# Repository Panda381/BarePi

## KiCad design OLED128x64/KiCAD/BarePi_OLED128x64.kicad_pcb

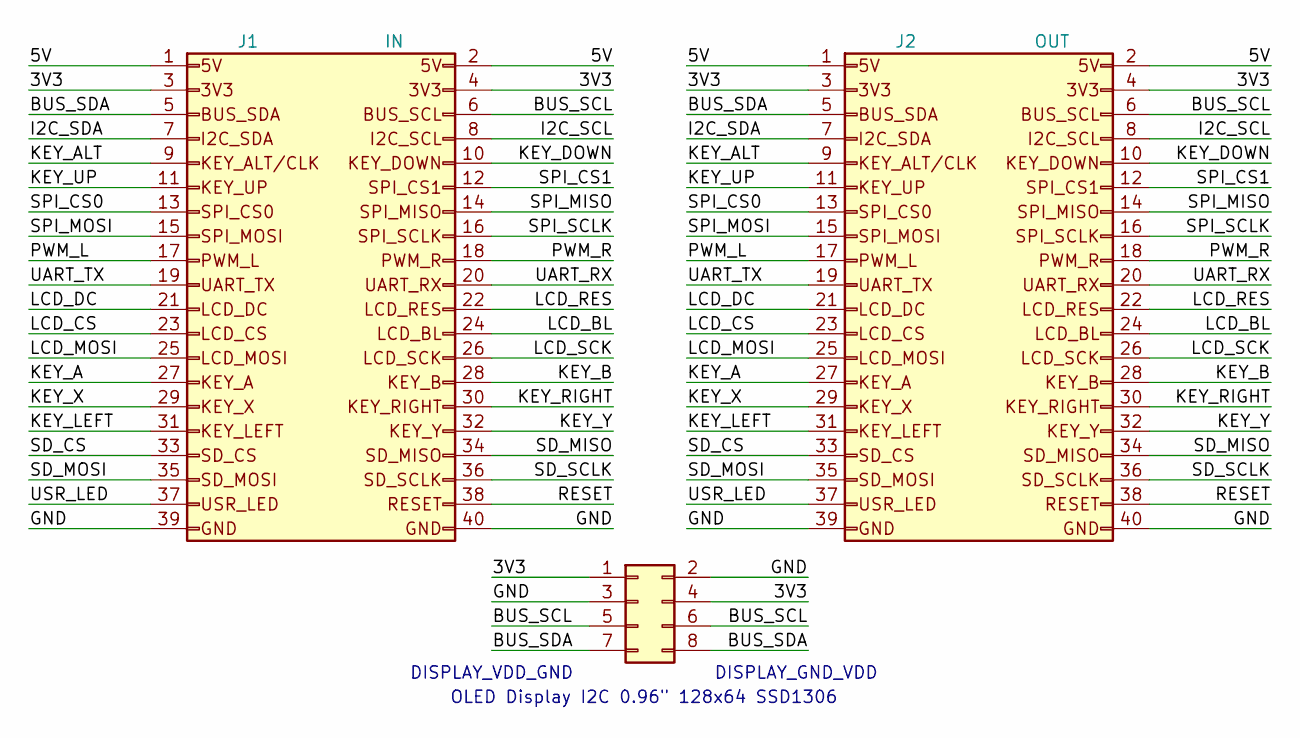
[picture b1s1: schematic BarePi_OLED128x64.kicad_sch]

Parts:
J1: IN; Raspberry_IN_PinHeader_2x20_P2.54mm_Horizontal
J2: OUT; Raspberry_OUT_PinSocket_2x20_P2.54mm_Horizontal
J3: DISPLAY; Raspberry_PinSocket_2x04_P2.54mm_Vertical

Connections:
/3V3: J1.3, J1.4, J2.3, J2.4, J3.1, J3.4
/5V: J1.1, J1.2, J2.1, J2.2
/BUS_SCL: J1.6, J2.6, J3.5, J3.6
/BUS_SDA: J1.5, J2.5, J3.7, J3.8
/GND: J1.39, J1.40, J2.39, J2.40, J3.2, J3.3
/I2C_SCL: J1.8, J2.8
/I2C_SDA: J1.7, J2.7
/KEY_A: J1.27, J2.27
/KEY_ALT: J1.9, J2.9
/KEY_B: J1.28, J2.28
/KEY_DOWN: J1.10, J2.10
/KEY_LEFT: J1.31, J2.31
/KEY_RIGHT: J1.30, J2.30
/KEY_UP: J1.11, J2.11
/KEY_X: J1.29, J2.29
/KEY_Y: J1.32, J2.32
/LCD_BL: J1.24, J2.24
/LCD_CS: J1.23, J2.23
/LCD_DC: J1.21, J2.21
/LCD_MOSI: J1.25, J2.25
/LCD_RES: J1.22, J2.22
/LCD_SCK: J1.26, J2.26
/PWM_L: J1.17, J2.17
/PWM_R: J1.18, J2.18
/RESET: J1.38, J2.38
/SD_CS: J1.33, J2.33
/SD_MISO: J1.34, J2.34
/SD_MOSI: J1.35, J2.35
/SD_SCLK: J1.36, J2.36
/SPI_CS0: J1.13, J2.13
/SPI_CS1: J1.12, J2.12
/SPI_MISO: J1.14, J2.14
/SPI_MOSI: J1.15, J2.15
/SPI_SCLK: J1.16, J2.16
/UART_RX: J1.20, J2.20
/UART_TX: J1.19, J2.19
/USR_LED: J1.37, J2.37

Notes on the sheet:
OLED Display I2C 0.96{dblquote} 128x64 SSD1306
DISPLAY_VDD_GND
DISPLAY_GND_VDD

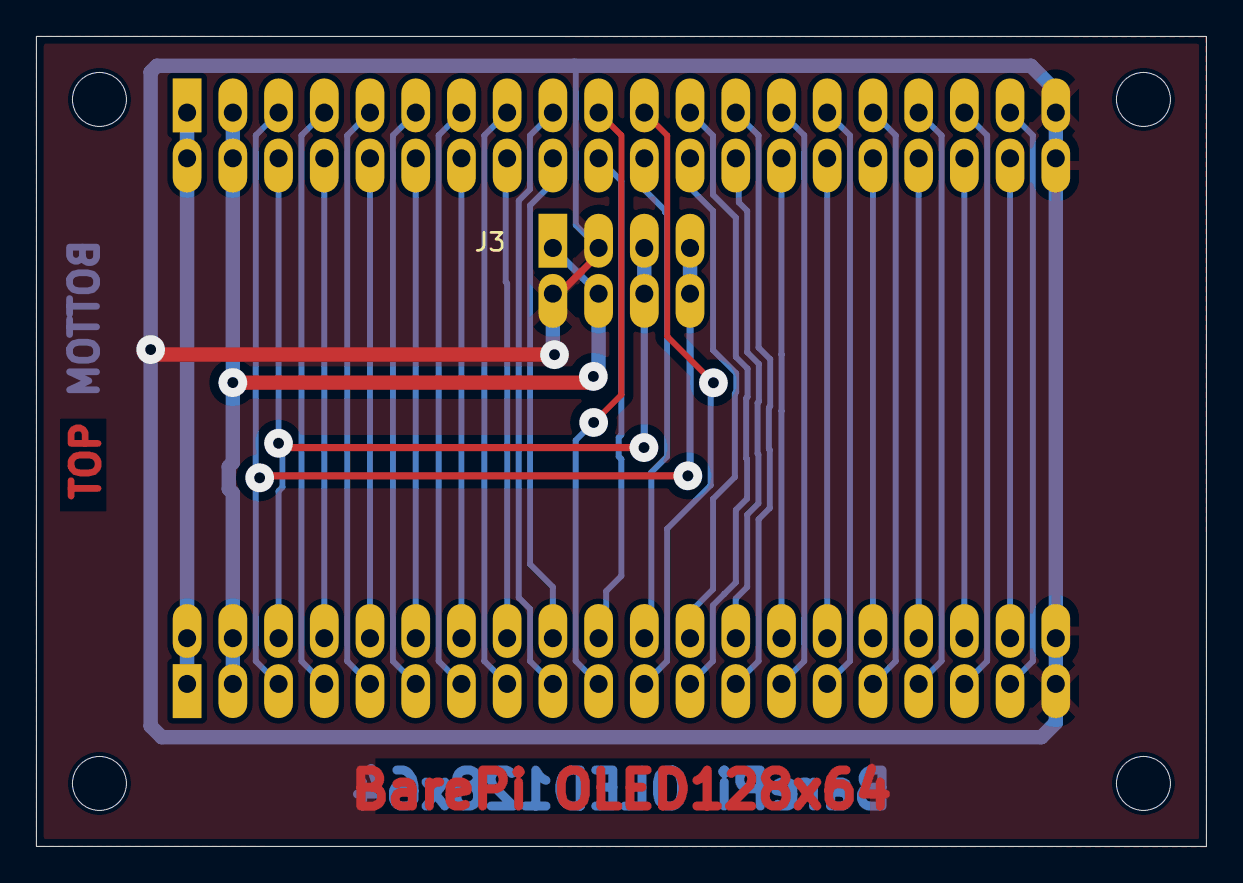
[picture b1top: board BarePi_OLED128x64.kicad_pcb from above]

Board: 2 copper layers, 65.0 x 45.0 mm, 3 parts (0 on the bottom side), 37 nets.

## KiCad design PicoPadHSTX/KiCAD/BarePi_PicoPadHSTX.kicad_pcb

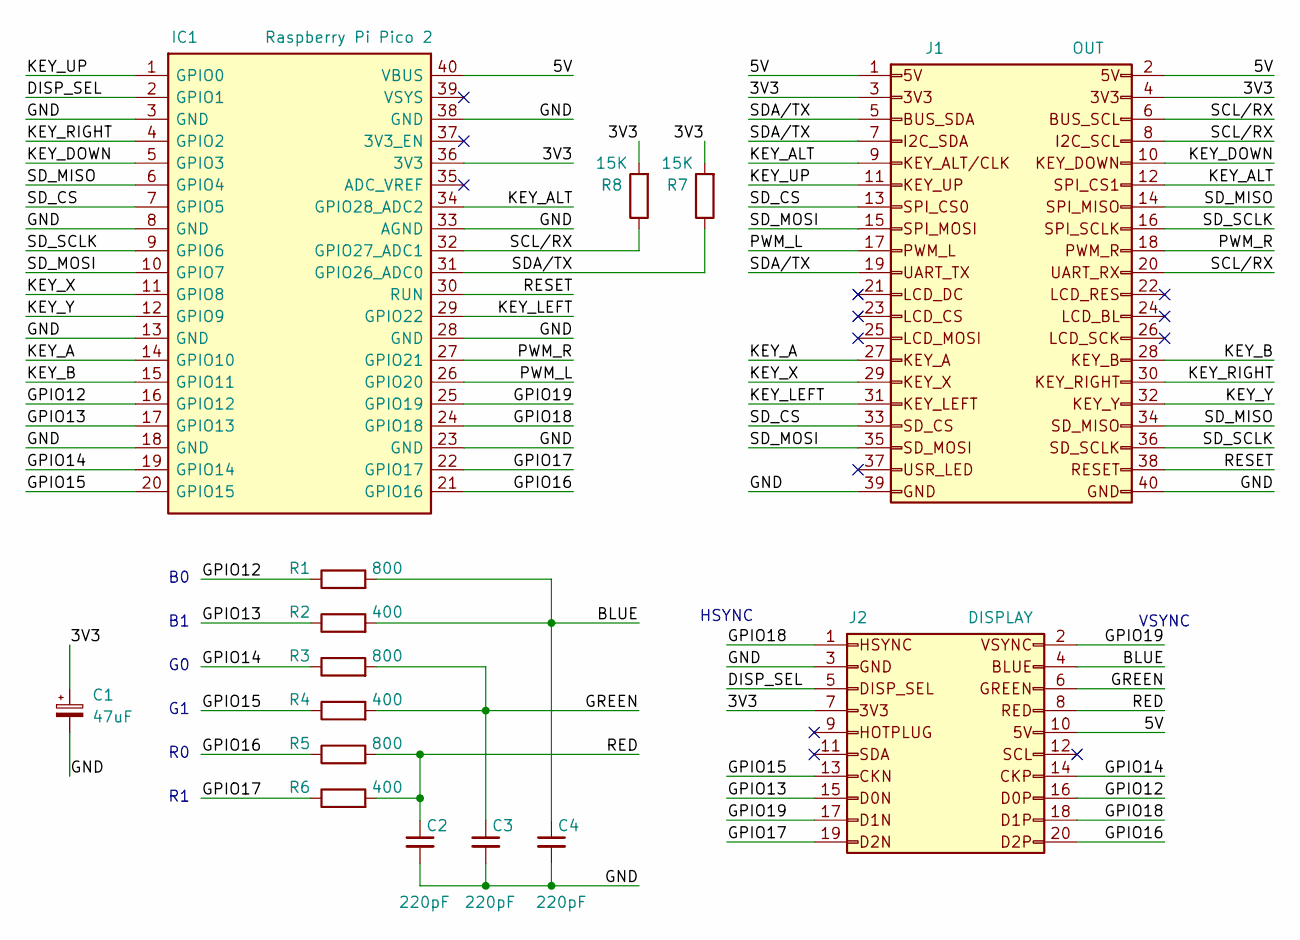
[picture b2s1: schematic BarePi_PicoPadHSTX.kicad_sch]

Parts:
C1: 47uF; CP_EIA-3216-18_Kemet-A_HandSolder
C2, C3, C4: 220pF; C_1206_3216Metric_Pad1.33x1.80mm_HandSolder
IC1: Raspberry Pi Pico 2; Raspberry_Pi_Pico_Common_Unspecified
J1: OUT; Raspberry_OUT_PinSocket_2x20_P2.54mm_Horizontal
J2: DISPLAY; Raspberry_OUT_PinSocket_2x10_P2.54mm_Horizontal
R1, R3, R5: 800; R_0805_2012Metric_Pad1.20x1.40mm_HandSolder
R2, R4, R6: 400; R_0805_2012Metric_Pad1.20x1.40mm_HandSolder
R7, R8: 15K; R_1206_3216Metric_Pad1.30x1.75mm_HandSolder

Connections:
/3V3: C1.1, IC1.36 (3V3), J1.3, J1.4, J2.7, R7.2, R8.2
/5V: IC1.40 (VBUS), J1.1, J1.2, J2.10
/BLUE: C4.1, J2.4, R1.2, R2.2
/DISP_SEL: IC1.2 (GPIO1), J2.5
/GND: C1.2, C2.2, C3.2, C4.2, IC1.3 (GND), IC1.8 (GND), IC1.13 (GND), IC1.18 (GND), IC1.23 (GND), IC1.28 (GND), IC1.33 (AGND), IC1.38 (GND), J1.39, J1.40, J2.3
/GPIO12: IC1.16 (GPIO12), J2.16, R1.1
/GPIO13: IC1.17 (GPIO13), J2.15, R2.1
/GPIO14: IC1.19 (GPIO14), J2.14, R3.1
/GPIO15: IC1.20 (GPIO15), J2.13, R4.1
/GPIO16: IC1.21 (GPIO16), J2.20, R5.1
/GPIO17: IC1.22 (GPIO17), J2.19, R6.1
/GPIO18: IC1.24 (GPIO18), J2.1, J2.18
/GPIO19: IC1.25 (GPIO19), J2.2, J2.17
/GREEN: C3.1, J2.6, R3.2, R4.2
/KEY_A: IC1.14 (GPIO10), J1.27
/KEY_ALT: IC1.34 (GPIO28_ADC2), J1.9, J1.12
/KEY_B: IC1.15 (GPIO11), J1.28
/KEY_DOWN: IC1.5 (GPIO3), J1.10
/KEY_LEFT: IC1.29 (GPIO22), J1.31
/KEY_RIGHT: IC1.4 (GPIO2), J1.30
/KEY_UP: IC1.1 (GPIO0), J1.11
/KEY_X: IC1.11 (GPIO8), J1.29
/KEY_Y: IC1.12 (GPIO9), J1.32
/PWM_L: IC1.26 (GPIO20), J1.17
/PWM_R: IC1.27 (GPIO21), J1.18
/RED: C2.1, J2.8, R5.2, R6.2
/RESET: IC1.30 (RUN), J1.38
/SCL/RX: IC1.32 (GPIO27_ADC1), J1.6, J1.8, J1.20, R8.1
/SDA/TX: IC1.31 (GPIO26_ADC0), J1.5, J1.7, J1.19, R7.1
/SD_CS: IC1.7 (GPIO5), J1.13, J1.33
/SD_MISO: IC1.6 (GPIO4), J1.14, J1.34
/SD_MOSI: IC1.10 (GPIO7), J1.15, J1.35
/SD_SCLK: IC1.9 (GPIO6), J1.16, J1.36

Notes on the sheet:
VSYNC
HSYNC

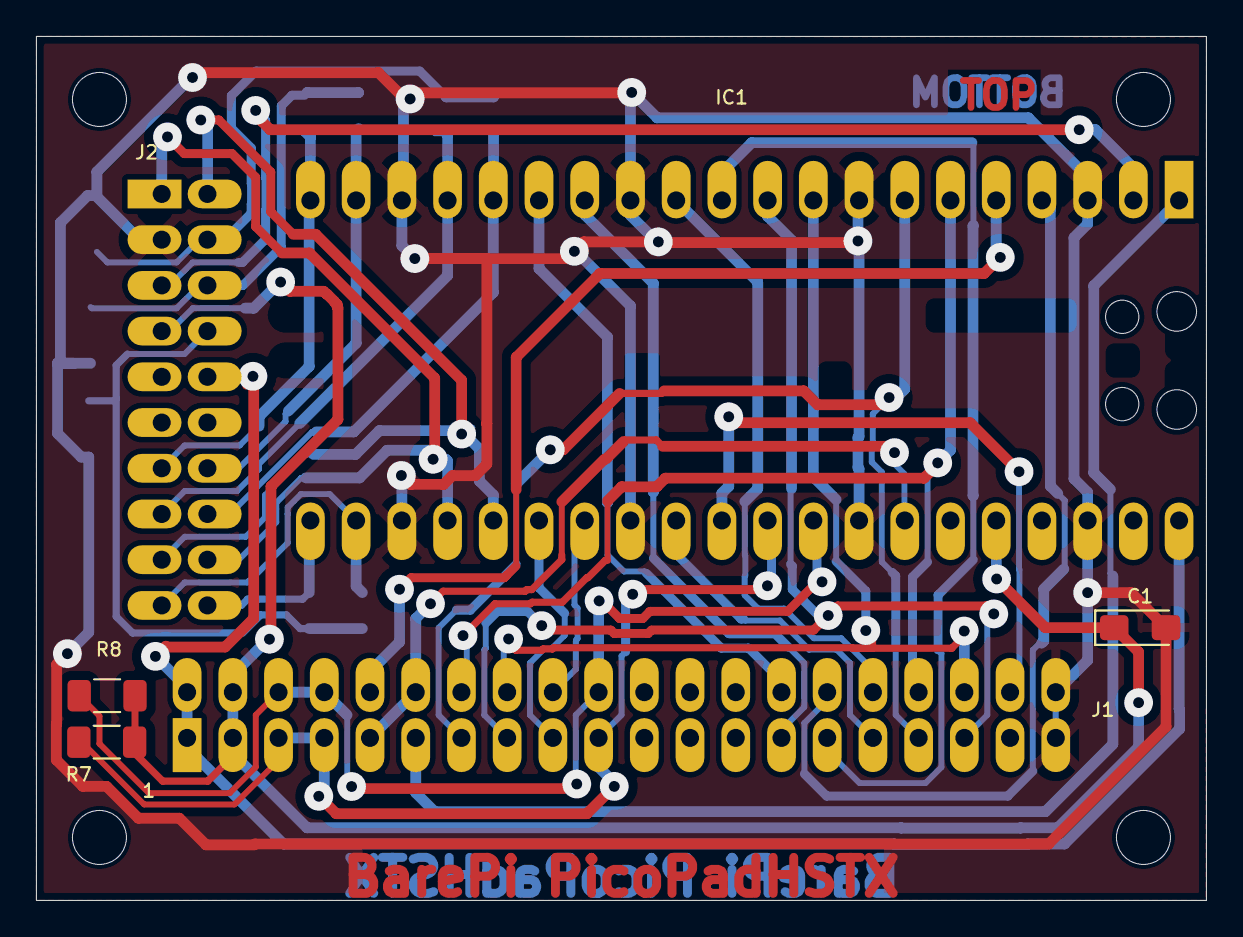
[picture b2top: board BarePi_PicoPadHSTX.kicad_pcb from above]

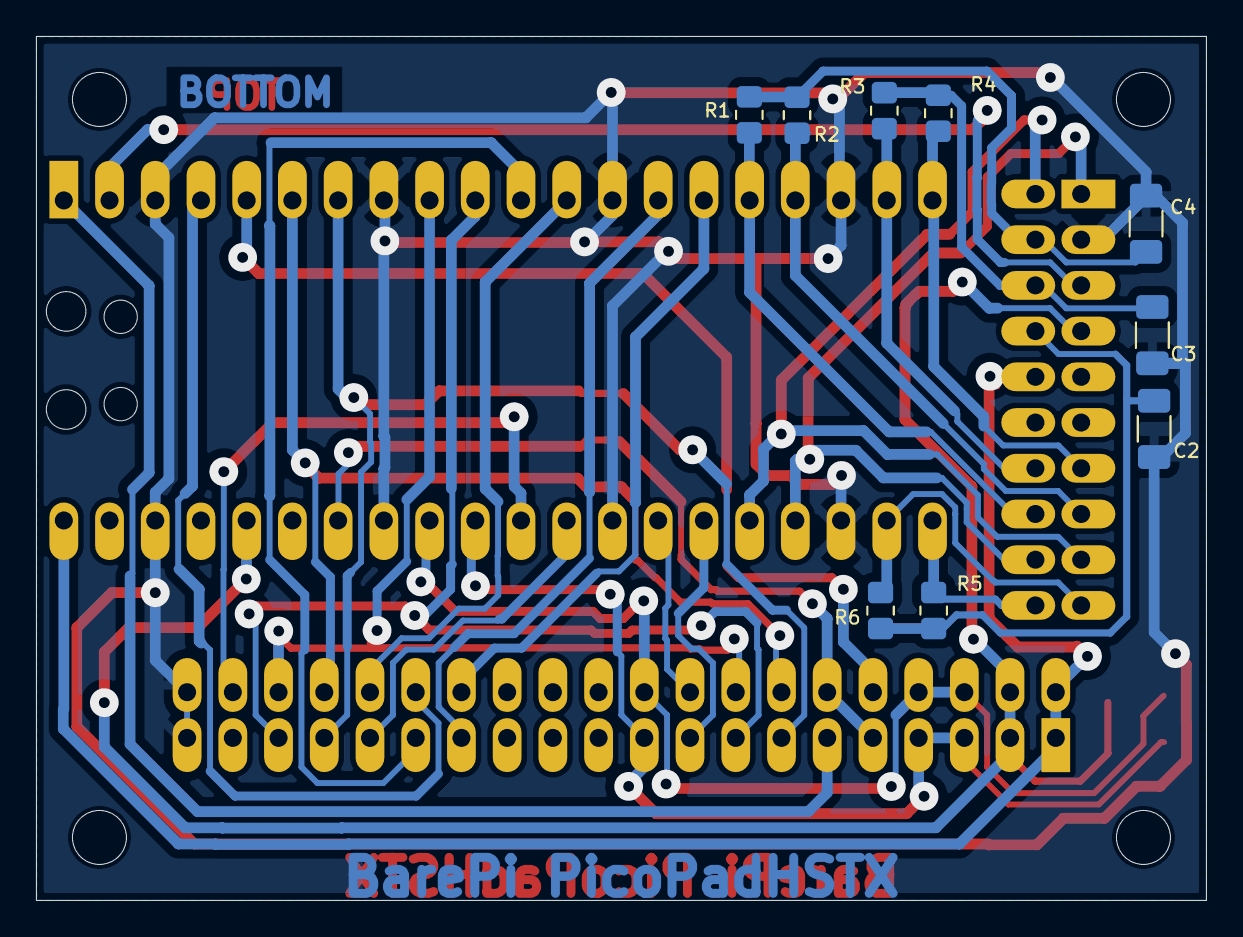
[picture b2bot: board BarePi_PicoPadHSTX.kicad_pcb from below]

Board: 2 copper layers, 65.0 x 48.0 mm, 15 parts (9 on the bottom side), 33 nets.

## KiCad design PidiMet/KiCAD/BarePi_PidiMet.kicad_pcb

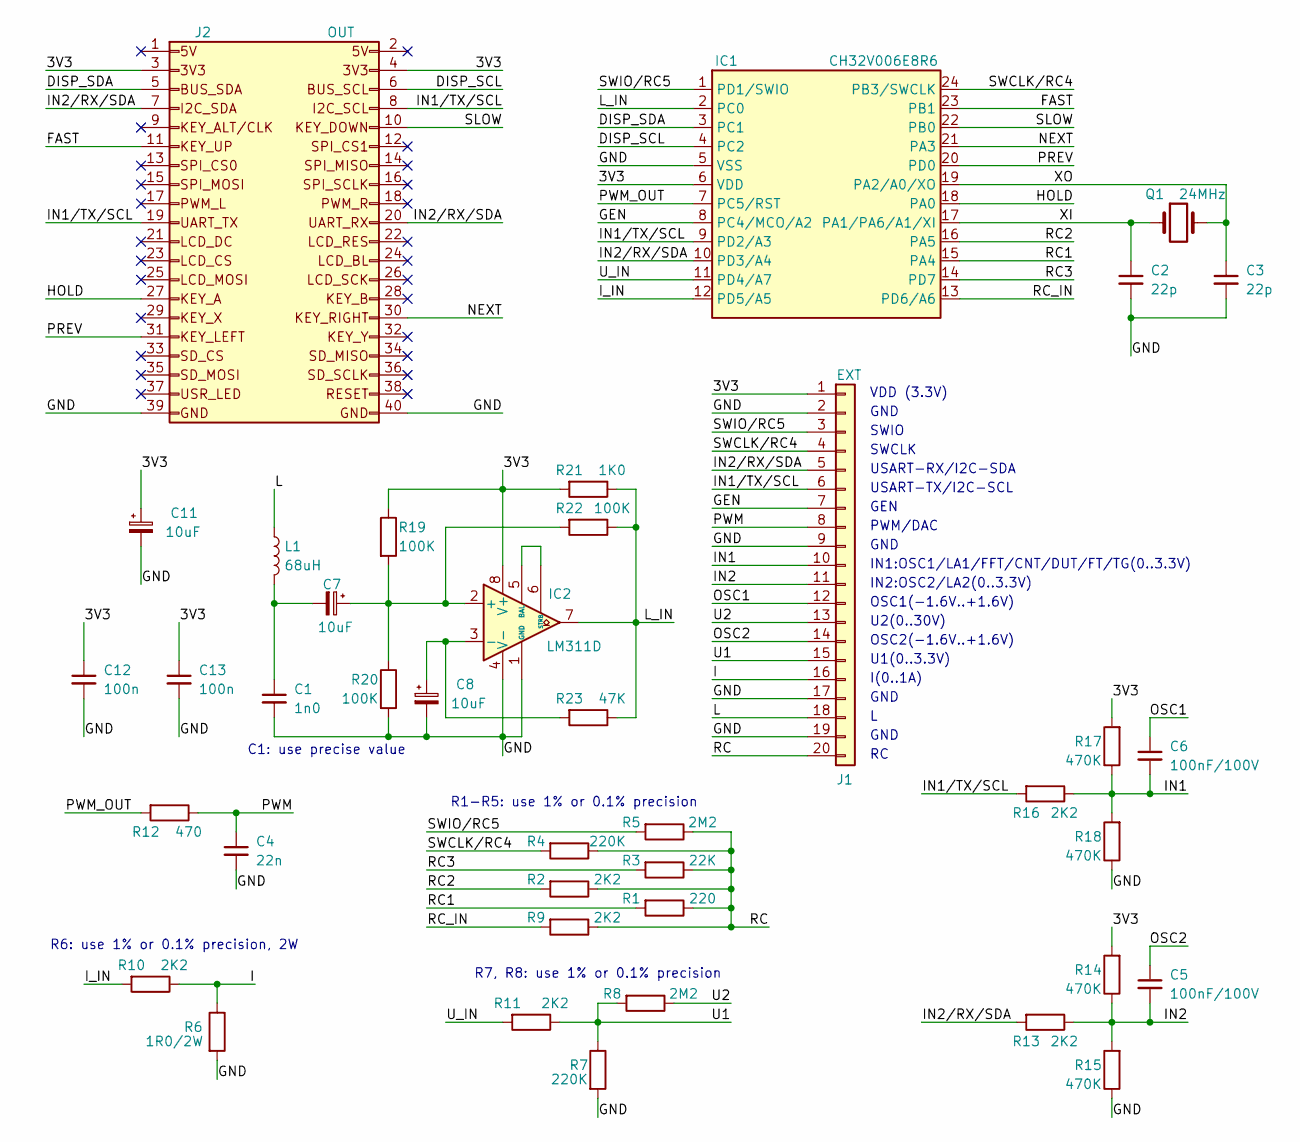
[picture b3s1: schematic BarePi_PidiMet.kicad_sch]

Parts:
C1: 1n0; C_Axial_L5.1mm_D3.1mm_P10.00mm_Horizontal
C2, C3: 22p; C_1206_3216Metric_Pad1.33x1.80mm_HandSolder
C4: 22n; C_1206_3216Metric_Pad1.33x1.80mm_HandSolder
C5, C6: 100nF/100V; C_1206_3216Metric_Pad1.33x1.80mm_HandSolder
C7, C8, C11: 10uF; CP_EIA-3216-18_Kemet-A_HandSolder
C12, C13: 100n; C_1206_3216Metric_Pad1.33x1.80mm_HandSolder
IC1: CH32V006E8R6; Raspberry_QSOP-24_3.9x8.7mm_P0.635mm
IC2: LM311D; JEITA_SOIC-8_3.9x4.9mm_P1.27mm
J1: EXT; Raspberry_PinHeader_1x20_P2.54mm_Horizontal_rev
J2: OUT; Raspberry_OUT_PinSocket_2x20_P2.54mm_Horizontal
L1: 68uH; L_Axial_L5.0mm_D3.6mm_P10.00mm_Horizontal_Murata_BL01RN1A2A2
Q1: 24MHz; Raspberry_Crystal_HC49-4H_Vertical
R1: 220; R_Axial_DIN0207_L6.3mm_D2.5mm_P7.62mm_Horizontal
R2: 2K2; R_Axial_DIN0207_L6.3mm_D2.5mm_P7.62mm_Horizontal
R3: 22K; R_Axial_DIN0207_L6.3mm_D2.5mm_P7.62mm_Horizontal
R4, R7: 220K; R_Axial_DIN0207_L6.3mm_D2.5mm_P7.62mm_Horizontal
R5, R8: 2M2; R_Axial_DIN0207_L6.3mm_D2.5mm_P7.62mm_Horizontal
R6: 1R0/2W; R_Axial_DIN0411_L9.9mm_D3.6mm_P12.70mm_Horizontal
R9, R10, R11, R13, R16: 2K2; R_0805_2012Metric_Pad1.20x1.40mm_HandSolder
R12: 470; R_0805_2012Metric_Pad1.20x1.40mm_HandSolder
R14, R15, R17, R18: 470K; R_0805_2012Metric_Pad1.20x1.40mm_HandSolder
R19, R20, R22: 100K; R_0805_2012Metric_Pad1.20x1.40mm_HandSolder
R21: 1K0; R_0805_2012Metric_Pad1.20x1.40mm_HandSolder
R23: 47K; R_0805_2012Metric_Pad1.20x1.40mm_HandSolder

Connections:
/3V3: C11.1, C12.1, C13.1, IC1.6 (VDD), IC2.8 (V+), J1.1, J2.3, J2.4, R14.2, R17.2, R19.1, R21.2
/DISP_SCL: IC1.4 (PC2), J2.6
/DISP_SDA: IC1.3 (PC1), J2.5
/FAST: IC1.23 (PB1), J2.11
/GEN: IC1.8 (PC4/MCO/A2), J1.7
/GND: C1.2, C2.2, C3.2, C4.2, C8.2, C11.2, C12.2, C13.2, IC1.5 (VSS), IC2.1 (GND), IC2.4 (V-), J1.2, J1.9, J1.17, J1.19, J2.39, J2.40, R6.2, R7.2, R15.1, R18.1, R20.2
/HOLD: IC1.18 (PA0), J2.27
/I: J1.16, R6.1, R10.1
/IN1: C6.2, J1.10, R16.1, R17.1, R18.2
/IN2: C5.2, J1.11, R13.1, R14.1, R15.2
/I_IN: IC1.12 (PD5/A5), R10.2
/L: J1.18, L1.1
/L_IN: IC1.2 (PC0), IC2.7, R21.1, R22.1, R23.1
/NEXT: IC1.21 (PA3), J2.30
/OSC1: C6.1, J1.12
/OSC2: C5.1, J1.14
/PREV: IC1.20 (PD0), J2.31
/PWM: C4.1, J1.8, R12.1
/PWM_OUT: IC1.7 (PC5/RST), R12.2
/RC: J1.20, R1.1, R2.1, R3.1, R4.1, R5.1, R9.1
/RC1: IC1.15 (PA4), R1.2
/RC2: IC1.16 (PA5), R2.2
/RC3: IC1.14 (PD7), R3.2
/RC_IN: IC1.13 (PD6/A6), R9.2
/SLOW: IC1.22 (PB0), J2.10
/SWCLK/RC4: IC1.24 (PB3/SWCLK), J1.4, R4.2
/SWIO/RC5: IC1.1 (PD1/SWIO), J1.3, R5.2
/U1: J1.15, R7.1, R8.2, R11.1
/U2: J1.13, R8.1
/U_IN: IC1.11 (PD4/A7), R11.2
/XI: C2.1, IC1.17 (PA1/PA6/A1/XI), Q1.1
/XO: C3.1, IC1.19 (PA2/A0/XO), Q1.2
unnamed: C1.1, C7.2, L1.2
unnamed: C7.1, IC2.2 (+), R19.2, R20.1, R22.2
unnamed: C8.1, IC2.3 (-), R23.2
unnamed: IC2.5 (BAL), IC2.6 (STRB)

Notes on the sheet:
OSC1(-1.6V..+1.6V)
GEN
VDD (3.3V)
U2(0..30V)
IN2:OSC2/LA2(0..3.3V)
USART-RX/I2C-SDA
SWIO
R1-R5: use 1% or 0.1% precision
R7, R8: use 1% or 0.1% precision
PWM/DAC
C1: use precise value
USART-TX/I2C-SCL
GND
U1(0..3.3V)
R6: use 1% or 0.1% precision, 2W
OSC2(-1.6V..+1.6V)
I(0..1A)
IN1:OSC1/LA1/FFT/CNT/DUT/FT/TG(0..3.3V)
SWCLK

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
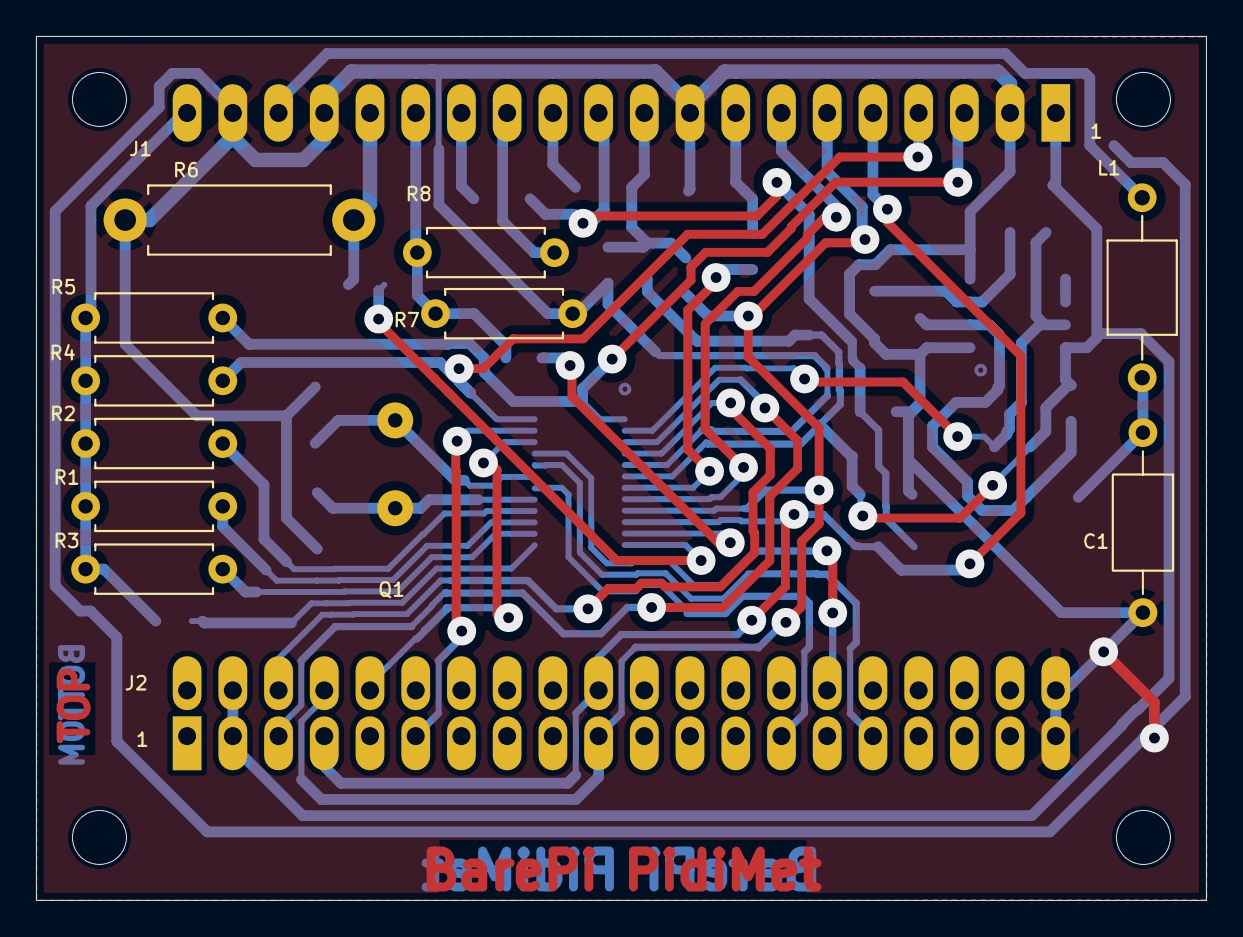
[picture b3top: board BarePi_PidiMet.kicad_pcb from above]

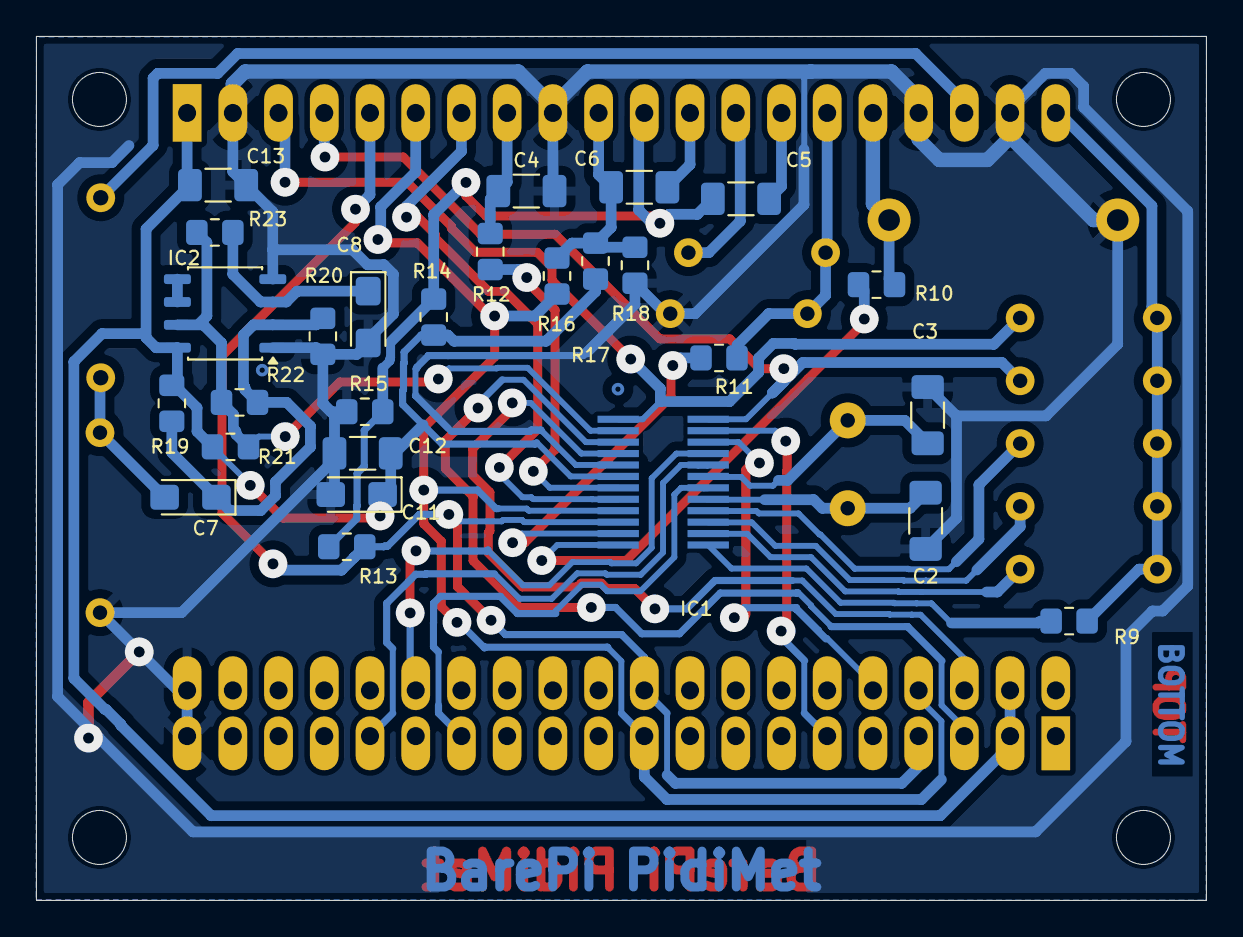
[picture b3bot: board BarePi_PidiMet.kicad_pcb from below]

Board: 2 copper layers, 65.0 x 48.0 mm, 40 parts (27 on the bottom side), 38 nets.

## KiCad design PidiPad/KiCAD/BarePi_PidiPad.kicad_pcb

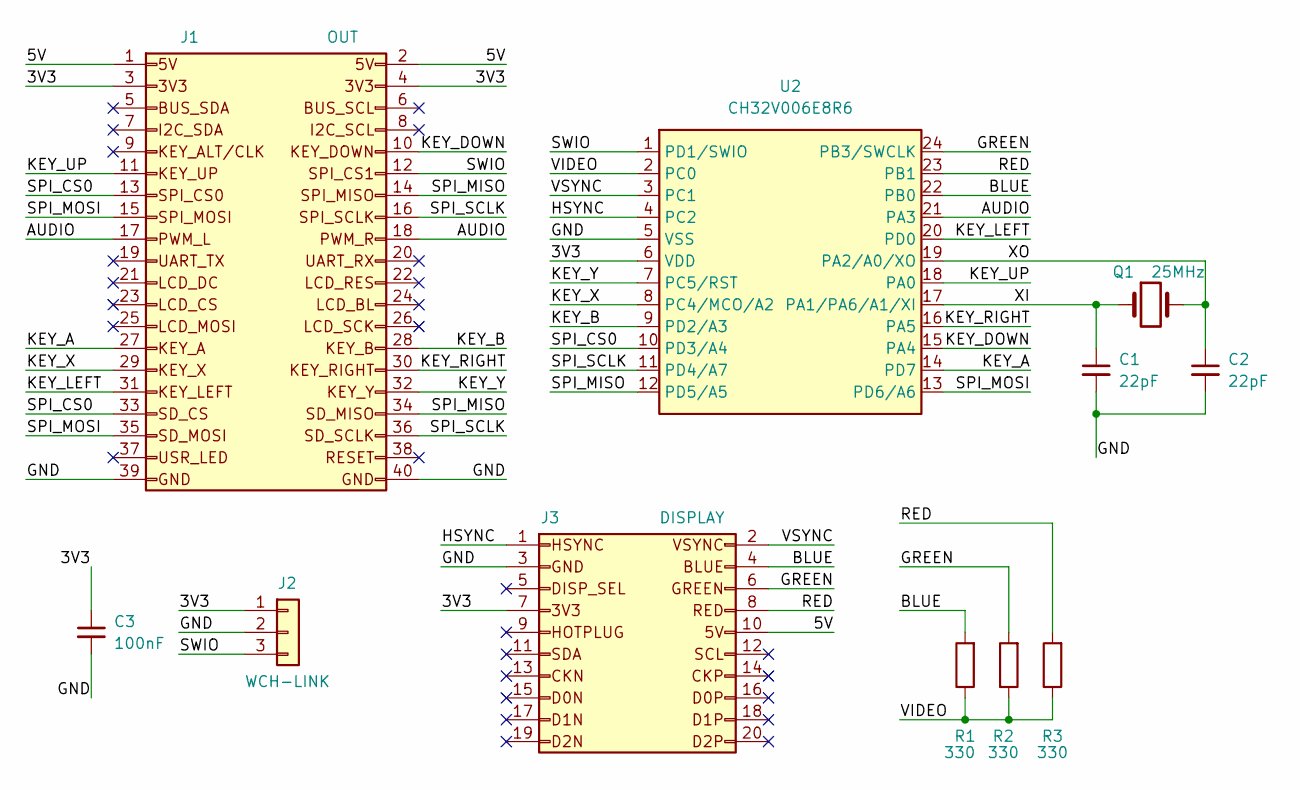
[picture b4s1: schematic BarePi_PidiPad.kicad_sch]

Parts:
C1, C2: 22pF; C_1206_3216Metric_Pad1.33x1.80mm_HandSolder
C3: 100nF; C_1206_3216Metric_Pad1.33x1.80mm_HandSolder
J1: OUT; Raspberry_OUT_PinSocket_2x20_P2.54mm_Horizontal
J2: WCH-LINK; Raspberry_PinHeader_1x03_P2.54mm_Horizontal
J3: DISPLAY; Raspberry_OUT_PinSocket_2x10_P2.54mm_Horizontal
Q1: 25MHz; Raspberry_Crystal_HC49-4H_Vertical
R1, R2, R3: 330; R_0805_2012Metric_Pad1.20x1.40mm_HandSolder
U2: CH32V006E8R6; Raspberry_QSOP-24_3.9x8.7mm_P0.635mm

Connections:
/3V3: C3.1, J1.3, J1.4, J2.1, J3.7, U2.6 (VDD)
/5V: J1.1, J1.2, J3.10
/AUDIO: J1.17, J1.18, U2.21 (PA3)
/BLUE: J3.4, R1.2, U2.22 (PB0)
/GND: C1.2, C2.2, C3.2, J1.39, J1.40, J2.2, J3.3, U2.5 (VSS)
/GREEN: J3.6, R2.2, U2.24 (PB3/SWCLK)
/HSYNC: J3.1, U2.4 (PC2)
/KEY_A: J1.27, U2.14 (PD7)
/KEY_B: J1.28, U2.9 (PD2/A3)
/KEY_DOWN: J1.10, U2.15 (PA4)
/KEY_LEFT: J1.31, U2.20 (PD0)
/KEY_RIGHT: J1.30, U2.16 (PA5)
/KEY_UP: J1.11, U2.18 (PA0)
/KEY_X: J1.29, U2.8 (PC4/MCO/A2)
/KEY_Y: J1.32, U2.7 (PC5/RST)
/RED: J3.8, R3.2, U2.23 (PB1)
/SPI_CS0: J1.13, J1.33, U2.10 (PD3/A4)
/SPI_MISO: J1.14, J1.34, U2.12 (PD5/A5)
/SPI_MOSI: J1.15, J1.35, U2.13 (PD6/A6)
/SPI_SCLK: J1.16, J1.36, U2.11 (PD4/A7)
/SWIO: J1.12, J2.3, U2.1 (PD1/SWIO)
/VIDEO: R1.1, R2.1, R3.1, U2.2 (PC0)
/VSYNC: J3.2, U2.3 (PC1)
/XI: C1.1, Q1.1, U2.17 (PA1/PA6/A1/XI)
/XO: C2.1, Q1.2, U2.19 (PA2/A0/XO)

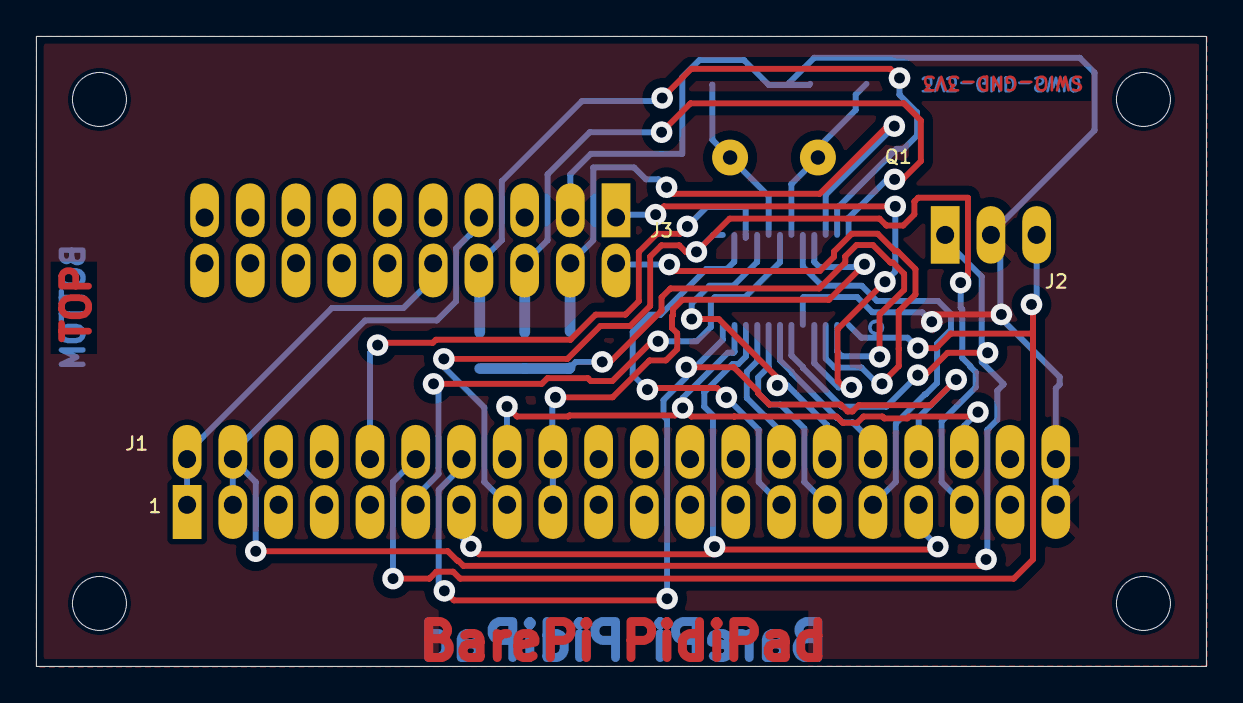
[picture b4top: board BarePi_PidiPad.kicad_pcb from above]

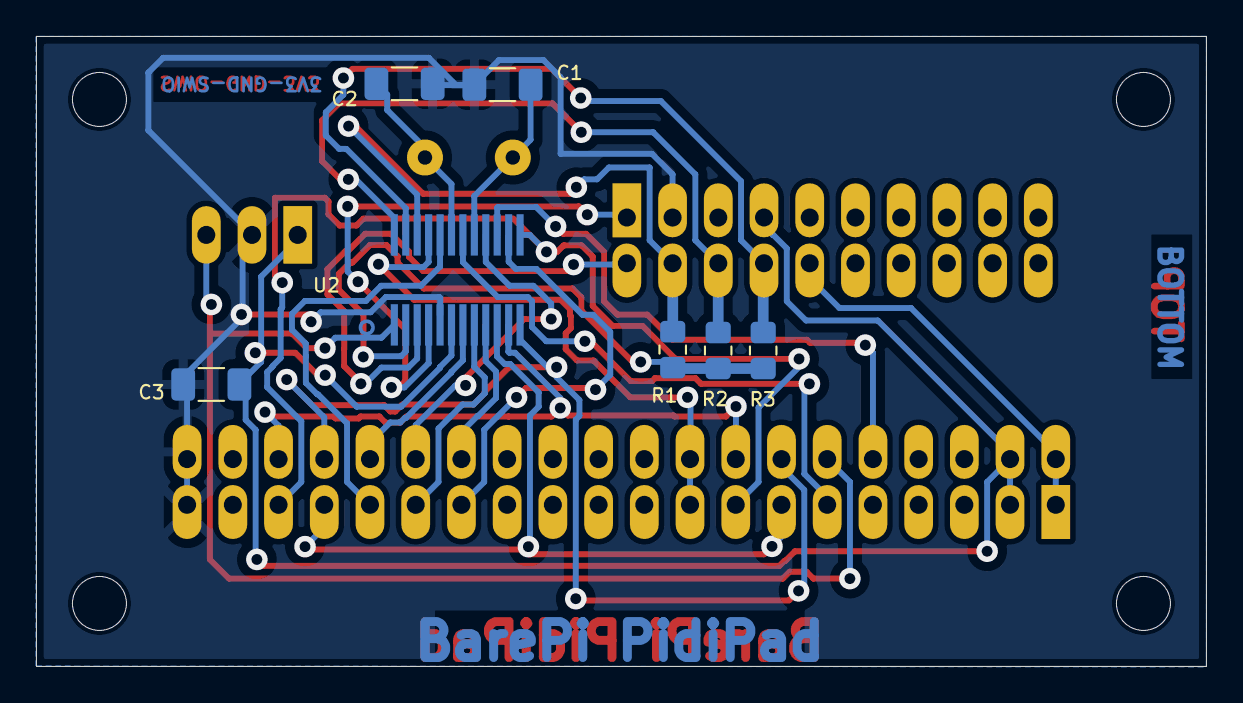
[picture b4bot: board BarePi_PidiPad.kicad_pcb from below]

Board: 2 copper layers, 65.0 x 35.0 mm, 11 parts (7 on the bottom side), 25 nets.

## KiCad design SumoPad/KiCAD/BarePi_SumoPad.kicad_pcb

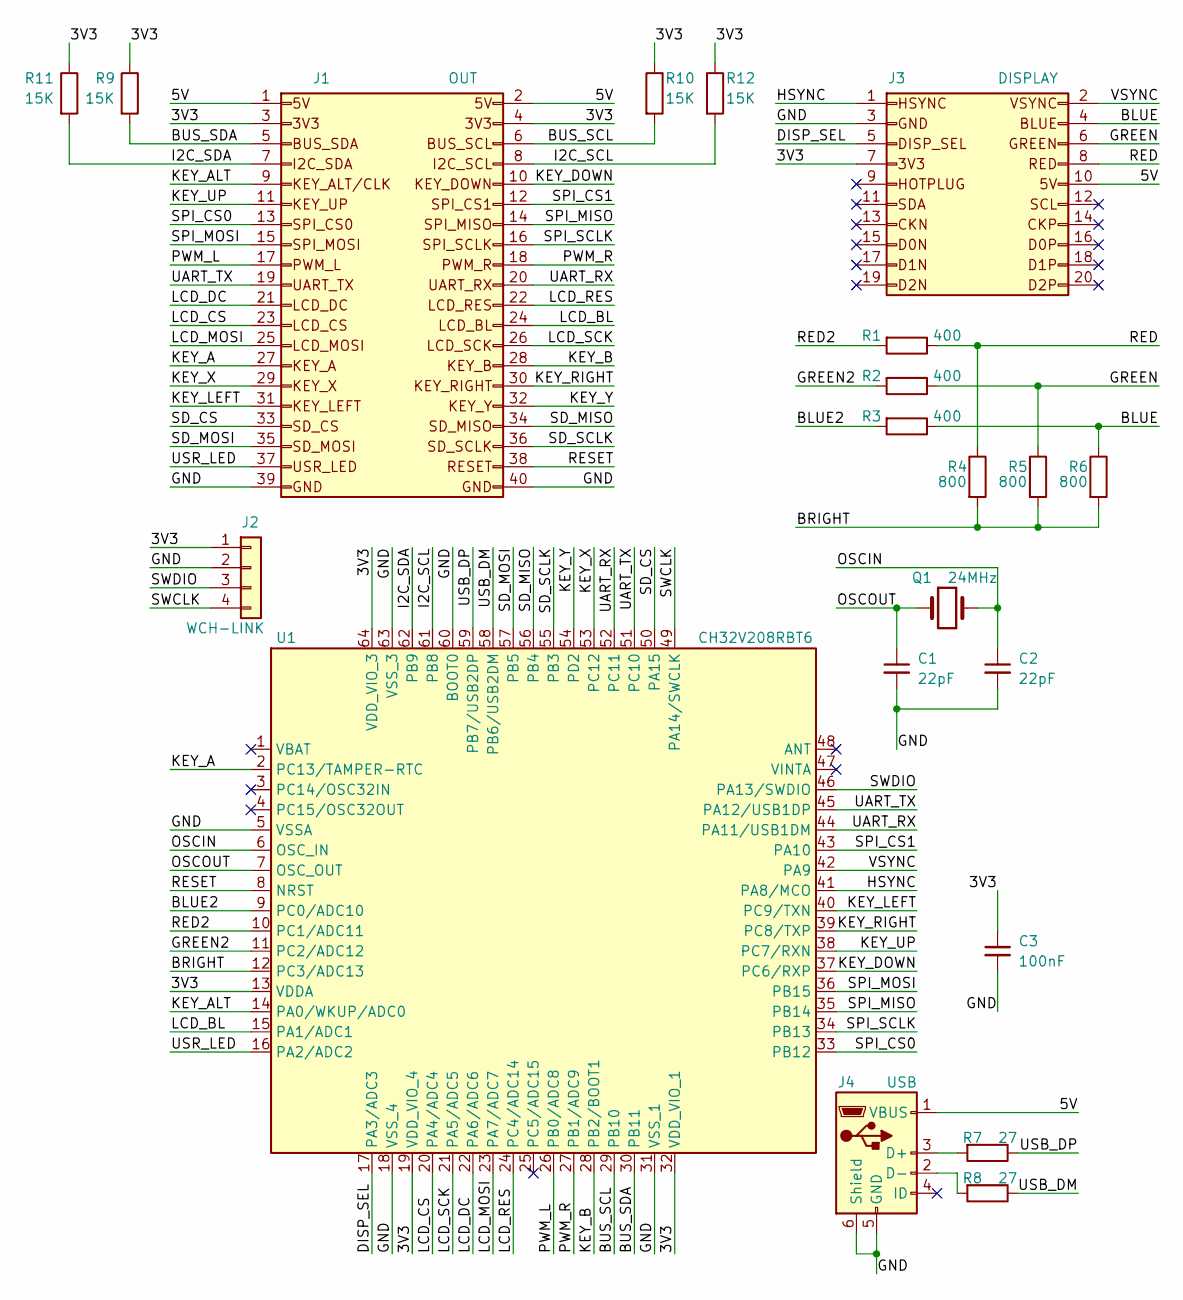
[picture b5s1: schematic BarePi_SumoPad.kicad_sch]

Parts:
C1, C2: 22pF; C_1206_3216Metric_Pad1.33x1.80mm_HandSolder
C3: 100nF; C_1206_3216Metric_Pad1.33x1.80mm_HandSolder
J1: OUT; Raspberry_OUT_PinSocket_2x20_P2.54mm_Horizontal
J2: WCH-LINK; Raspberry_PinHeader_1x04_P2.54mm_Horizontal
J3: DISPLAY; Raspberry_OUT_PinSocket_2x10_P2.54mm_Horizontal
J4: USB; Raspberry_USB_Micro-B_Amphenol_10104110_Horizontal
Q1: 24MHz; Raspberry_Crystal_HC49-4H_Vertical
R1, R2, R3: 400; R_0805_2012Metric_Pad1.20x1.40mm_HandSolder
R4, R5, R6: 800; R_0805_2012Metric_Pad1.20x1.40mm_HandSolder
R7, R8: 27; R_0805_2012Metric_Pad1.20x1.40mm_HandSolder
R9, R10, R11, R12: 15K; R_1206_3216Metric_Pad1.30x1.75mm_HandSolder
U1: CH32V208RBT6; Raspberry_LQFP-64_10x10mm_P0.5mm_adapter

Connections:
/3V3: C3.1, J1.3, J1.4, J2.1, J3.7, R9.1, R10.1, R11.1, R12.1, U1.13 (VDDA), U1.19 (VDD_VIO_4), U1.32 (VDD_VIO_1), U1.64 (VDD_VIO_3)
/5V: J1.1, J1.2, J3.10, J4.1 (VBUS)
/BLUE: J3.4, R3.1, R6.1
/BLUE2: R3.2, U1.9 (PC0/ADC10)
/BRIGHT: R4.2, R5.2, R6.2, U1.12 (PC3/ADC13)
/BUS_SCL: J1.6, R10.2, U1.29 (PB10)
/BUS_SDA: J1.5, R9.2, U1.30 (PB11)
/DISP_SEL: J3.5, U1.17 (PA3/ADC3)
/GND: C1.2, C2.2, C3.2, J1.39, J1.40, J2.2, J3.3, J4.5 (GND), J4.6 (Shield), U1.5 (VSSA), U1.18 (VSS_4), U1.31 (VSS_1), U1.60 (BOOT0), U1.63 (VSS_3)
/GREEN: J3.6, R2.1, R5.1
/GREEN2: R2.2, U1.11 (PC2/ADC12)
/HSYNC: J3.1, U1.41 (PA8/MCO)
/I2C_SCL: J1.8, R12.2, U1.61 (PB8)
/I2C_SDA: J1.7, R11.2, U1.62 (PB9)
/KEY_A: J1.27, U1.2 (PC13/TAMPER-RTC)
/KEY_ALT: J1.9, U1.14 (PA0/WKUP/ADC0)
/KEY_B: J1.28, U1.28 (PB2/BOOT1)
/KEY_DOWN: J1.10, U1.37 (PC6/RXP)
/KEY_LEFT: J1.31, U1.40 (PC9/TXN)
/KEY_RIGHT: J1.30, U1.39 (PC8/TXP)
/KEY_UP: J1.11, U1.38 (PC7/RXN)
/KEY_X: J1.29, U1.53 (PC12)
/KEY_Y: J1.32, U1.54 (PD2)
/LCD_BL: J1.24, U1.15 (PA1/ADC1)
/LCD_CS: J1.23, U1.20 (PA4/ADC4)
/LCD_DC: J1.21, U1.22 (PA6/ADC6)
/LCD_MOSI: J1.25, U1.23 (PA7/ADC7)
/LCD_RES: J1.22, U1.24 (PC4/ADC14)
/LCD_SCK: J1.26, U1.21 (PA5/ADC5)
/OSCIN: C2.1, Q1.2, U1.6 (OSC_IN)
/OSCOUT: C1.1, Q1.1, U1.7 (OSC_OUT)
/PWM_L: J1.17, U1.26 (PB0/ADC8)
/PWM_R: J1.18, U1.27 (PB1/ADC9)
/RED: J3.8, R1.1, R4.1
/RED2: R1.2, U1.10 (PC1/ADC11)
/RESET: J1.38, U1.8 (NRST)
/SD_CS: J1.33, U1.50 (PA15)
/SD_MISO: J1.34, U1.56 (PB4)
/SD_MOSI: J1.35, U1.57 (PB5)
/SD_SCLK: J1.36, U1.55 (PB3)
/SPI_CS0: J1.13, U1.33 (PB12)
/SPI_CS1: J1.12, U1.43 (PA10)
/SPI_MISO: J1.14, U1.35 (PB14)
/SPI_MOSI: J1.15, U1.36 (PB15)
/SPI_SCLK: J1.16, U1.34 (PB13)
/SWCLK: J2.4, U1.49 (PA14/SWCLK)
/SWDIO: J2.3, U1.46 (PA13/SWDIO)
/UART_RX: J1.20, U1.44 (PA11/USB1DM), U1.52 (PC11)
/UART_TX: J1.19, U1.45 (PA12/USB1DP), U1.51 (PC10)
/USB_DM: R8.1, U1.58 (PB6/USB2DM)
/USB_DP: R7.1, U1.59 (PB7/USB2DP)
/USR_LED: J1.37, U1.16 (PA2/ADC2)
/VSYNC: J3.2, U1.42 (PA9)
unnamed: J4.3 (D+), R7.2
unnamed: J4.2 (D-), R8.2
